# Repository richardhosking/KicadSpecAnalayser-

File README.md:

# KicadSpecAnalayser-
KICAD Files for Spectrum Analyser design
Feb 9 2020 
Front end drafted

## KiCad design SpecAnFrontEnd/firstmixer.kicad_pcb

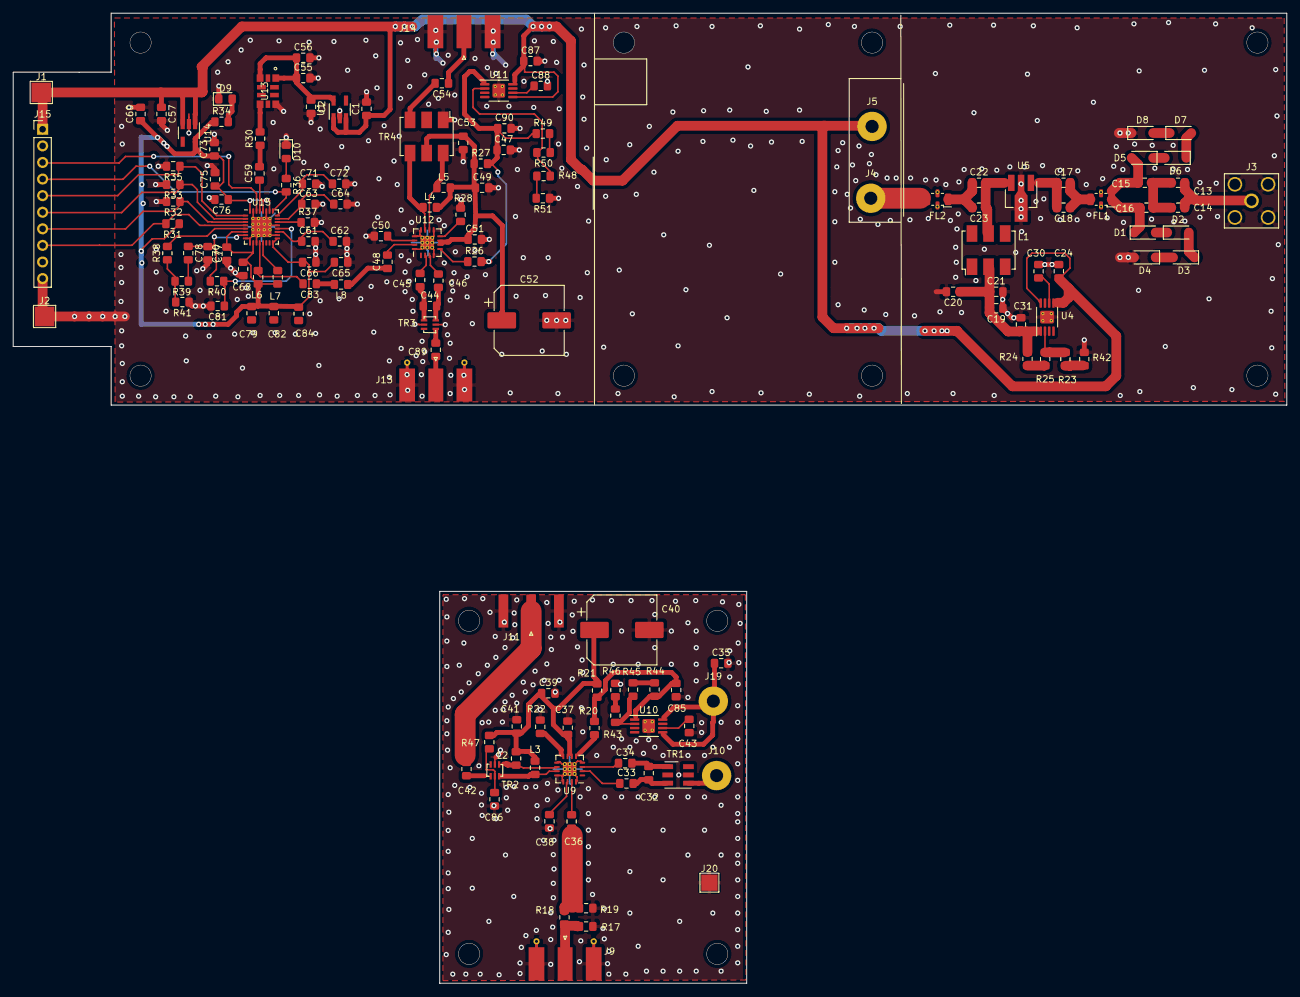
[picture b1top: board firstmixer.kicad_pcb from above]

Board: 2 copper layers, 195.0 x 148.5 mm, 151 parts (0 on the bottom side), 90 nets.

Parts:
C1, C2, C19, C39, C51, C57, C60: 1u; C_0805_2012Metric_Pad1.15x1.40mm_HandSolder
C13, C16, C18, C23, C33, C34, C36, C38, C55, C62, C64, C65, C72, C73, C75, C84: 100n; C_0805_2012Metric_Pad1.15x1.40mm_HandSolder
C14, C15, C17, C21, C22, C45, C46, C48, C50, C56, C79, C82: 100p; C_0805_2012Metric_Pad1.15x1.40mm_HandSolder
C20, C30, C37, C41, C43, C47, C49, C53, C86, C88: 10n; C_0805_2012Metric_Pad1.15x1.40mm_HandSolder
C24, C31, C35, C85, C87, C90: 10u; C_0805_2012Metric_Pad1.15x1.40mm_HandSolder
C32, C44: 0.6p; C_0805_2012Metric_Pad1.15x1.40mm_HandSolder
C40, C52: 220u; CP_Elec_10x10.5
C42, C89: 4p7; C_0805_2012Metric_Pad1.15x1.40mm_HandSolder
C54, C59, C83: 1n; C_0805_2012Metric_Pad1.15x1.40mm_HandSolder
C61, C63, C66, C68, C70, C71, C76: 10p; C_0805_2012Metric_Pad1.15x1.40mm_HandSolder
C77: 2n7; C_0805_2012Metric_Pad1.15x1.40mm_HandSolder
C78: 47n; C_0805_2012Metric_Pad1.15x1.40mm_HandSolder
C81: 680p; C_0805_2012Metric_Pad1.15x1.40mm_HandSolder
D1, D2, D3, D4, D5, D6, D7, D8: MMSD301T1G; D_SOD-123
D9: Power; D_0805_2012Metric_Pad1.15x1.40mm_HandSolder
D10: LOCK; D_0805_2012Metric_Pad1.15x1.40mm_HandSolder
FL1, FL2: LFCN-2600; Filter_Mini-Circuits_FV1206
J1: +V; TestPoint_Pad_3.0x3.0mm
J2: TestPoint_Pad_3.0x3.0mm
J3: Input; SMA_Amphenol_132203-12_Horizontal
J4: OUT to First Mixer; SolderWirePad_1x01_Drill2mm
J5, J19: +V; SolderWirePad_1x01_Drill2mm
J9: LO IN; SMA_Molex_73251-1153_EdgeMount_Horizontal
J10: Conn_Coaxial; SolderWirePad_1x01_Drill2mm
J11: Conn_Coaxial; SMA_Amphenol_132289_EdgeMount
J13, J14: Conn_Coaxial; SMA_Molex_73251-1153_EdgeMount_Horizontal
J15: Data; PinHeader_1x10_P2.54mm_Vertical
J20: GND; TestPoint_Pad_2.5x2.5mm
L1: ADCH-80+; Mini-Circuits_CD542_H2.84mm
L2, L3: 2nH; L_0805_2012Metric_Pad1.15x1.40mm_HandSolder
L4, L5: 22n; L_0805_2012Metric_Pad1.15x1.40mm_HandSolder
L6, L7: 7n5; L_0805_2012Metric_Pad1.15x1.40mm_HandSolder
L8: 1n9; L_0805_2012Metric_Pad1.15x1.40mm_HandSolder
R17, R19, R38: DNI; R_0805_2012Metric_Pad1.15x1.40mm_HandSolder
R18, R30, R41, R47: 0R; R_0805_2012Metric_Pad1.15x1.40mm_HandSolder
R20, R26, R31, R32, R33, R35: 10K; R_0805_2012Metric_Pad1.15x1.40mm_HandSolder
R21, R27: 0.5R; R_0805_2012Metric_Pad1.15x1.40mm_HandSolder
R22, R28: 4K75; R_0805_2012Metric_Pad1.15x1.40mm_HandSolder
R23, R43, R48: 22K; R_0805_2012Metric_Pad1.15x1.40mm_HandSolder
R24, R44, R49: 68K; R_0805_2012Metric_Pad1.15x1.40mm_HandSolder
R25, R45, R50: 8K2; R_0805_2012Metric_Pad1.15x1.40mm_HandSolder
R34, R36: 100R; R_0805_2012Metric_Pad1.15x1.40mm_HandSolder
R37: 4K7; R_0805_2012Metric_Pad1.15x1.40mm_HandSolder
R39: 360R; R_0805_2012Metric_Pad1.15x1.40mm_HandSolder
R40: 1K; R_0805_2012Metric_Pad1.15x1.40mm_HandSolder
R42, R46, R51: 1K8; R_0805_2012Metric_Pad1.15x1.40mm_HandSolder
TR1: TCM1-63AX; Mini-Circuits_DB1627
TR2, TR3: NCS1-422; Minicircuits_GE0805C-1
TR4: ADT4-5WT; Mini-Circuits_CD637_H5.23mm
U1, U14: ADP150; SOT-23-5_HandSoldering
U4, U10, U11: TPSA49; MSOP-8-1EP_3x3mm_P0.65mm_EP1.95x2.15mm_ThermalVias
U5: MMG38151; SOT-89-3_Handsoldering
U9, U12: LTC5510; QFN-16-1EP_4x4mm_P0.65mm_EP2.1x2.1mm_ThermalVias
U13: SiT5156
U15: ADF4351; LFCSP-32-1EP_5x5mm_P0.5mm_EP3.1x3.1mm_ThermalVias

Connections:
+V: C1.1, C24.1, C35.1, C57.1, C87.1, J1.1, J5.1, J15.1, J19.1, U1.1, U1.3, U4.5, U4.8, U10.5, U10.8, U11.5, U11.8, U14.1, U14.3
/First Mixer/U9VCC: C37.1, C39.1, C40.1, C41.1, L2.2, L3.1, R21.1, R47.1, U9.6, U9.7
/Second LO/AVDD2LO: C60.1, C65.2, C66.2, C68.2, C70.2, C73.1, C75.1, C76.1, C79.1, C82.1, C84.1, L6.2, L7.1, R31.1, R34.1, U14.5, U15.6, U15.10, U15.16, U15.17, U15.26, U15.28, U15.32
/Second LO/AVDDOSC: C2.1, C55.1, C56.1, U1.5, U13.1, U13.9
GND: C1.2, C2.2, C19.1, C20.2, C21.2, C24.2, C30.2, C31.2, C35.2, C37.2, C38.1, C39.2, C40.2, C41.2, C43.2, C47.2, C49.2, C50.1, C51.2, C52.2, C53.2, C55.2, C56.2, C57.2, C60.2, C61.2, C62.2, C63.2, C64.2, C65.1, C66.1, C68.1, C70.1, C71.2, C72.2, C73.2, C75.2, C76.2, C77.2, C81.2, C85.2, C86.2, C87.2, C88.2, C90.2, D4.2, D8.1, D9.1, D10.1, FL1.2, FL1.4, FL2.2, FL2.4, J2.1, J3.2, J9.2, J11.2, J13.2, J14.2, J15.10, J20.1, R17.2, R19.2, R22.2, R28.2, R32.2, R33.2, R35.2, R37.2, R41.1, R42.1, R46.1, R51.1, TR1.2, TR2.5, TR3.2, TR3.5, TR4.1, U1.2, U4.9, U5.2, U9.4, U9.9, U9.12, U9.13, U9.16, U9.17, U10.9, U11.9, U12.4, U12.9, U12.12, U12.13, U12.16, U12.17, U13.4, U14.2, U15.8, U15.9, U15.11, U15.18, U15.21, U15.27, U15.31, U15.33
LO: C48.1, L8.1
unnamed: C13.1, C14.2, J3.1
unnamed: C13.2, C14.1, C15.2, C16.1
unnamed: C15.1, C16.2, D1.1, D5.2, FL1.1
unnamed: C17.1, C18.2, U5.1
unnamed: C17.2, C18.1, FL1.3
unnamed: C19.2, C20.1, C21.1, C31.1, L1.2, R24.1, U4.1
unnamed: C22.1, C23.2, FL2.1
unnamed: C22.2, C23.1, L1.5, U5.3
unnamed: C30.1, U4.6
unnamed: C32.1, C33.2, TR1.4
unnamed: C32.2, C34.2, TR1.6
unnamed: C33.1, U9.2
unnamed: C34.1, U9.3
unnamed: C36.1, R18.1, R19.1
unnamed: C36.2, U9.15
unnamed: C38.2, U9.14
unnamed: C42.1, J11.1
unnamed: C42.2, TR2.1
unnamed: C43.1, U10.6
unnamed: C44.1, C45.2, TR3.4
unnamed: C44.2, C46.2, TR3.3
unnamed: C45.1, U12.2
unnamed: C46.1, U12.3
unnamed: C47.1, C90.1, R26.2, R27.2, R49.1, U11.1
unnamed: C48.2, U12.15
unnamed: C49.1, C51.1, C52.1, C53.1, L4.2, L5.2, R27.1, TR4.5, U12.6, U12.7
unnamed: C50.2, U12.14
unnamed: C54.1, J14.1
unnamed: C54.2, TR4.3
unnamed: C59.1, U15.29
unnamed: C59.2, R30.1
unnamed: C61.1, C62.1, U15.19
unnamed: C63.1, C64.1, U15.23
unnamed: C71.1, C72.1, U15.24
unnamed: C77.1, C78.1, R40.2, U15.7
unnamed: C78.2, R39.1
unnamed: C79.2, C82.2, C84.2
unnamed: C81.1, R40.1, U15.20
unnamed: C83.1, L8.2
unnamed: C83.2, L6.1, U15.12
unnamed: C85.1, R20.2, R21.2, R44.1, U10.1
unnamed: C86.1, R47.2, TR2.2
unnamed: C88.1, U11.6
unnamed: C89.1, TR3.1
unnamed: C89.2, J13.1
unnamed: D1.2, D2.1
unnamed: D2.2, D3.1
unnamed: D3.2, D4.1
unnamed: D5.1, D6.2
unnamed: D6.1, D7.2
unnamed: D7.1, D8.2
unnamed: D9.2, R34.2
unnamed: D10.2, R36.1
unnamed: FL2.3, J4.1
unnamed: J9.1, R17.1, R18.2
unnamed: J10.1, TR1.3
unnamed: J15.3, U15.30
unnamed: J15.4, R36.2, U15.25
unnamed: J15.5, R35.1, U15.1
unnamed: J15.6, R33.1, U15.2
unnamed: J15.7, R32.1, U15.3
unnamed: J15.8, R31.2, U15.4
unnamed: L2.1, TR2.3, U9.11
unnamed: L3.2, TR2.4, U9.10
unnamed: L4.1, TR4.4, U12.11
unnamed: L5.1, TR4.6, U12.10
unnamed: L7.2, U15.13
unnamed: R20.1, U9.5
unnamed: R22.1, U9.8
unnamed: R23.1, R42.2
unnamed: R23.2, R25.2, U4.2
unnamed: R24.2, R25.1
unnamed: R26.1, U12.5
unnamed: R28.1, U12.8
unnamed: R30.2, U13.6
unnamed: R37.1, U15.22
unnamed: R38.1, R39.2, R41.2
unnamed: R38.2, U15.5
unnamed: R43.1, R46.2
unnamed: R43.2, R45.2, U10.2
unnamed: R44.2, R45.1
unnamed: R48.1, R51.2
unnamed: R48.2, R50.2, U11.2
unnamed: R49.2, R50.1

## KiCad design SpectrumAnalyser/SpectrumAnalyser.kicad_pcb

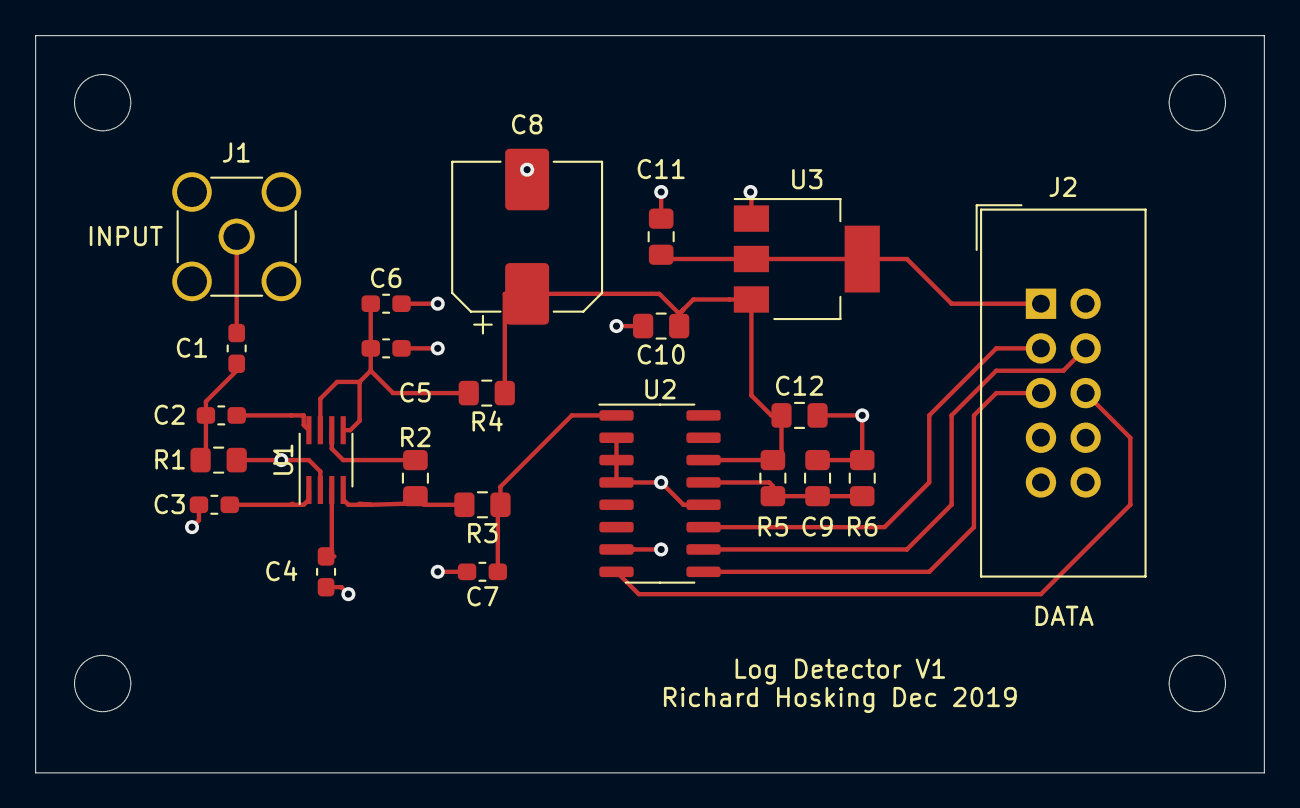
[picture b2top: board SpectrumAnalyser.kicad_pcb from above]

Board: 2 copper layers, 69.8 x 41.9 mm, 23 parts (0 on the bottom side), 17 nets.

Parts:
C1, C6: 100n; C_0603_1608Metric_Pad1.05x0.95mm_HandSolder
C2, C3, C5: 10n; C_0603_1608Metric_Pad1.05x0.95mm_HandSolder
C4: 1u; C_0603_1608Metric_Pad1.05x0.95mm_HandSolder
C7: 100p; C_0603_1608Metric_Pad1.05x0.95mm_HandSolder
C8: 10u; CP_Elec_8x10
C9, C10, C11: 100n; C_0805_2012Metric_Pad1.15x1.40mm_HandSolder
C12: 10n; C_0805_2012Metric_Pad1.15x1.40mm_HandSolder
J1: Input; SMA_Amphenol_901-144_Vertical
J2: DATA; IDC-Header_2x05_P2.54mm_Vertical
R1: 52R3; R_0805_2012Metric_Pad1.15x1.40mm_HandSolder
R2: 12K2; R_0805_2012Metric_Pad1.15x1.40mm_HandSolder
R3, R5: 100R; R_0805_2012Metric_Pad1.15x1.40mm_HandSolder
R4: 4R7; R_0805_2012Metric_Pad1.15x1.40mm_HandSolder
R6: 1K; R_0805_2012Metric_Pad1.15x1.40mm_HandSolder
U1: AD8310; SSOP-8_2.95x2.8mm_P0.65mm
U2: MCP3004; SOIC-16_3.9x9.9mm_P1.27mm
U3: NCP1117-3.3_SOT223; SOT-223-3_TabPin2

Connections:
GND: C3.2, C4.2, C5.2, C6.2, C7.2, C8.2, C9.2, C10.2, C11.2, C12.2, J1.2, J2.10, R1.2, R6.2, U1.2, U2.2, U2.3, U2.4, U2.7, U2.12, U3.1
unnamed: C1.1, C2.2, R1.1
unnamed: C1.2, J1.1
unnamed: C2.1, U1.8
unnamed: C3.1, U1.1
unnamed: C4.1, U1.3
unnamed: C5.1, C6.1, R4.2, U1.5, U1.7
unnamed: C7.1, R3.1, U2.1
unnamed: C9.1, R5.1, R6.1, U2.13
unnamed: C8.1, C10.1, C12.1, R4.1, R5.2, U2.14, U3.3
unnamed: C11.1, J2.1, U3.2
unnamed: J2.3, U2.11
unnamed: J2.4, U2.10
unnamed: J2.5, U2.9
unnamed: J2.6, U2.8
unnamed: R2.1, R3.2, U1.4
unnamed: R2.2, U1.6

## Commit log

2020-02-05 KICAD Feb 2020
    KIcad files
2020-02-09 Feb 9 2020
    Front end board drafted
2020-05-24 Front end and RF amp first LO
2020-05-24 Frontend RF amp second LO
2020-10-31 Delete MCP3004.pdf
    Device datafile
